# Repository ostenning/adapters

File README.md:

# adapters
A collection of smd to through-hole adapters

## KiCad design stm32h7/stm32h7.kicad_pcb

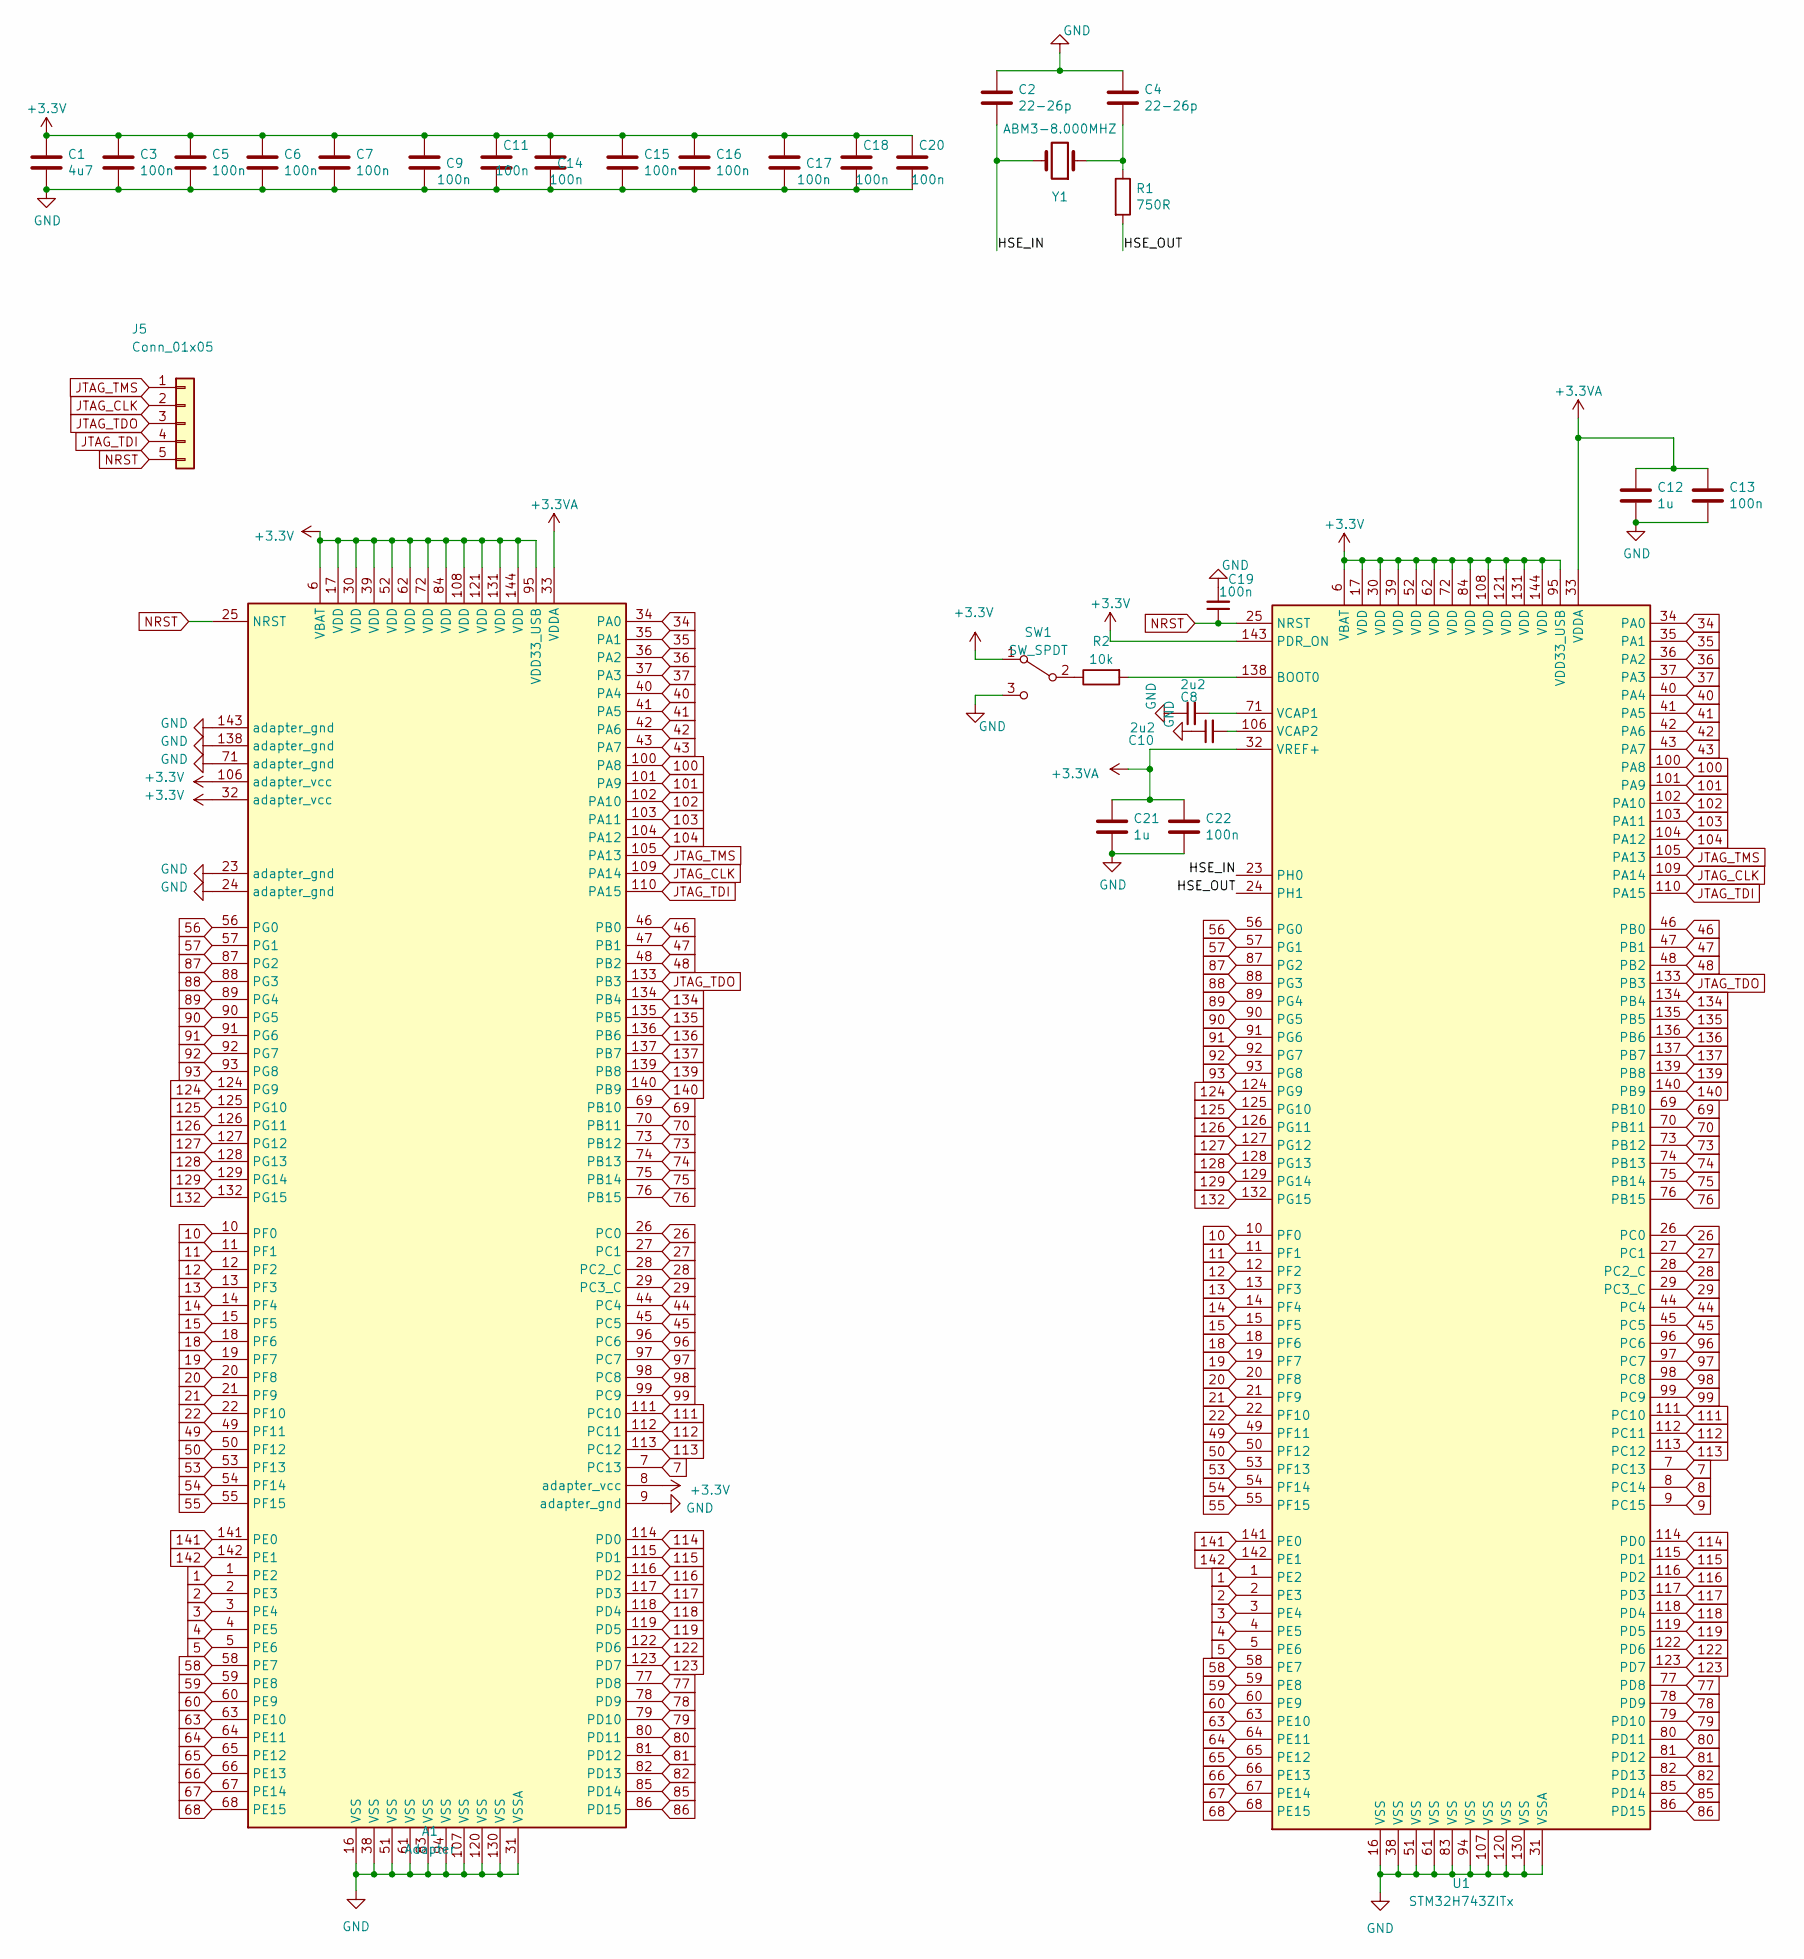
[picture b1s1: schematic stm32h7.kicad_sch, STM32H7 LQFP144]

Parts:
A1: Adapter; stm32h7_adapter
C1: 4u7; C_0603_1608Metric; LCSC Part # C19666
C2, C4: 22-26p; C_0402_1005Metric; LCSC Part # C388039
C3, C5, C6, C7, C9, C11, C13, C14, C15, C16, C17, C18, C20, C22: 100n; C_0603_1608Metric; LCSC Part # C14663
C8, C10: 2u2; C_0603_1608Metric; LCSC C23630
C12, C21: 1u; C_0603_1608Metric; LCSC Part # C15849
C19: 100n; C_0603_1608Metric; LCSC C14663
J5: Conn_01x05; PinHeader_1x05_P2.00mm_Vertical
R1: 750R; R_0603_1608Metric; LCSC Part # C23241
R2: 10k; R_0603_1608Metric; LCSC C25804
SW1: SW_SPDT; PinHeader_1x03_P2.54mm_Vertical
U1: STM32H743ZITx; LQFP-144_20x20mm_P0.5mm
Y1: ABM3-8.000MHZ; Crystal_SMD_Abracon_ABM3-2Pin_5.0x3.2mm_HandSoldering

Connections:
1: A1.1 (PE2), U1.1 (PE2)
2: A1.2 (PE3), U1.2 (PE3)
3: A1.3 (PE4), U1.3 (PE4)
4: A1.4 (PE5), U1.4 (PE5)
5: A1.5 (PE6), U1.5 (PE6)
7: A1.7 (PC13), U1.7 (PC13)
10: A1.10 (PF0), U1.10 (PF0)
11: A1.11 (PF1), U1.11 (PF1)
12: A1.12 (PF2), U1.12 (PF2)
13: A1.13 (PF3), U1.13 (PF3)
14: A1.14 (PF4), U1.14 (PF4)
15: A1.15 (PF5), U1.15 (PF5)
18: A1.18 (PF6), U1.18 (PF6)
19: A1.19 (PF7), U1.19 (PF7)
20: A1.20 (PF8), U1.20 (PF8)
21: A1.21 (PF9), U1.21 (PF9)
22: A1.22 (PF10), U1.22 (PF10)
26: A1.26 (PC0), U1.26 (PC0)
27: A1.27 (PC1), U1.27 (PC1)
28: A1.28 (PC2_C), U1.28 (PC2_C)
29: A1.29 (PC3_C), U1.29 (PC3_C)
34: A1.34 (PA0), U1.34 (PA0)
35: A1.35 (PA1), U1.35 (PA1)
36: A1.36 (PA2), U1.36 (PA2)
37: A1.37 (PA3), U1.37 (PA3)
40: A1.40 (PA4), U1.40 (PA4)
41: A1.41 (PA5), U1.41 (PA5)
42: A1.42 (PA6), U1.42 (PA6)
43: A1.43 (PA7), U1.43 (PA7)
44: A1.44 (PC4), U1.44 (PC4)
45: A1.45 (PC5), U1.45 (PC5)
46: A1.46 (PB0), U1.46 (PB0)
47: A1.47 (PB1), U1.47 (PB1)
48: A1.48 (PB2), U1.48 (PB2)
49: A1.49 (PF11), U1.49 (PF11)
50: A1.50 (PF12), U1.50 (PF12)
53: A1.53 (PF13), U1.53 (PF13)
54: A1.54 (PF14), U1.54 (PF14)
55: A1.55 (PF15), U1.55 (PF15)
56: A1.56 (PG0), U1.56 (PG0)
57: A1.57 (PG1), U1.57 (PG1)
58: A1.58 (PE7), U1.58 (PE7)
59: A1.59 (PE8), U1.59 (PE8)
60: A1.60 (PE9), U1.60 (PE9)
63: A1.63 (PE10), U1.63 (PE10)
64: A1.64 (PE11), U1.64 (PE11)
65: A1.65 (PE12), U1.65 (PE12)
66: A1.66 (PE13), U1.66 (PE13)
67: A1.67 (PE14), U1.67 (PE14)
68: A1.68 (PE15), U1.68 (PE15)
69: A1.69 (PB10), U1.69 (PB10)
70: A1.70 (PB11), U1.70 (PB11)
73: A1.73 (PB12), U1.73 (PB12)
74: A1.74 (PB13), U1.74 (PB13)
75: A1.75 (PB14), U1.75 (PB14)
76: A1.76 (PB15), U1.76 (PB15)
77: A1.77 (PD8), U1.77 (PD8)
78: A1.78 (PD9), U1.78 (PD9)
79: A1.79 (PD10), U1.79 (PD10)
80: A1.80 (PD11), U1.80 (PD11)
81: A1.81 (PD12), U1.81 (PD12)
82: A1.82 (PD13), U1.82 (PD13)
85: A1.85 (PD14), U1.85 (PD14)
86: A1.86 (PD15), U1.86 (PD15)
87: A1.87 (PG2), U1.87 (PG2)
88: A1.88 (PG3), U1.88 (PG3)
89: A1.89 (PG4), U1.89 (PG4)
90: A1.90 (PG5), U1.90 (PG5)
91: A1.91 (PG6), U1.91 (PG6)
92: A1.92 (PG7), U1.92 (PG7)
93: A1.93 (PG8), U1.93 (PG8)
96: A1.96 (PC6), U1.96 (PC6)
97: A1.97 (PC7), U1.97 (PC7)
98: A1.98 (PC8), U1.98 (PC8)
99: A1.99 (PC9), U1.99 (PC9)
100: A1.100 (PA8), U1.100 (PA8)
101: A1.101 (PA9), U1.101 (PA9)
102: A1.102 (PA10), U1.102 (PA10)
103: A1.103 (PA11), U1.103 (PA11)
104: A1.104 (PA12), U1.104 (PA12)
111: A1.111 (PC10), U1.111 (PC10)
112: A1.112 (PC11), U1.112 (PC11)
113: A1.113 (PC12), U1.113 (PC12)
114: A1.114 (PD0), U1.114 (PD0)
115: A1.115 (PD1), U1.115 (PD1)
116: A1.116 (PD2), U1.116 (PD2)
117: A1.117 (PD3), U1.117 (PD3)
118: A1.118 (PD4), U1.118 (PD4)
119: A1.119 (PD5), U1.119 (PD5)
122: A1.122 (PD6), U1.122 (PD6)
123: A1.123 (PD7), U1.123 (PD7)
124: A1.124 (PG9), U1.124 (PG9)
125: A1.125 (PG10), U1.125 (PG10)
126: A1.126 (PG11), U1.126 (PG11)
127: A1.127 (PG12), U1.127 (PG12)
128: A1.128 (PG13), U1.128 (PG13)
129: A1.129 (PG14), U1.129 (PG14)
132: A1.132 (PG15), U1.132 (PG15)
134: A1.134 (PB4), U1.134 (PB4)
135: A1.135 (PB5), U1.135 (PB5)
136: A1.136 (PB6), U1.136 (PB6)
137: A1.137 (PB7), U1.137 (PB7)
139: A1.139 (PB8), U1.139 (PB8)
140: A1.140 (PB9), U1.140 (PB9)
141: A1.141 (PE0), U1.141 (PE0)
142: A1.142 (PE1), U1.142 (PE1)
+3.3VA: A1.33 (VDDA), C12.1, C13.1, C21.1, C22.1, U1.32 (VREF+), U1.33 (VDDA)
+3V3: A1.6 (VBAT), A1.8 (adapter_vcc), A1.17 (VDD), A1.30 (VDD), A1.32 (adapter_vcc), A1.39 (VDD), A1.52 (VDD), A1.62 (VDD), A1.72 (VDD), A1.84 (VDD), A1.95 (VDD33_USB), A1.106 (adapter_vcc), A1.108 (VDD), A1.121 (VDD), A1.131 (VDD), A1.144 (VDD), C1.1, C3.1, C5.1, C6.1, C7.1, C9.1, C11.1, C14.1, C15.1, C16.1, C17.1, C18.1, C20.1, SW1.1 (A), U1.6 (VBAT), U1.17 (VDD), U1.30 (VDD), U1.39 (VDD), U1.52 (VDD), U1.62 (VDD), U1.72 (VDD), U1.84 (VDD), U1.95 (VDD33_USB), U1.108 (VDD), U1.121 (VDD), U1.131 (VDD), U1.143 (PDR_ON), U1.144 (VDD)
/HSE_IN: C2.2, U1.23 (PH0), Y1.2
/HSE_OUT: R1.2, U1.24 (PH1)
GND: A1.9 (adapter_gnd), A1.16 (VSS), A1.23 (adapter_gnd), A1.24 (adapter_gnd), A1.31 (VSSA), A1.38 (VSS), A1.51 (VSS), A1.61 (VSS), A1.71 (adapter_gnd), A1.83 (VSS), A1.94 (VSS), A1.107 (VSS), A1.120 (VSS), A1.130 (VSS), A1.138 (adapter_gnd), A1.143 (adapter_gnd), C1.2, C2.1, C3.2, C4.1, C5.2, C6.2, C7.2, C8.1, C9.2, C10.1, C11.2, C12.2, C13.2, C14.2, C15.2, C16.2, C17.2, C18.2, C19.2, C20.2, C21.2, C22.2, SW1.3 (C), U1.16 (VSS), U1.31 (VSSA), U1.38 (VSS), U1.51 (VSS), U1.61 (VSS), U1.83 (VSS), U1.94 (VSS), U1.107 (VSS), U1.120 (VSS), U1.130 (VSS)
JTAG_CLK: A1.109 (PA14), J5.2, U1.109 (PA14)
JTAG_TDI: A1.110 (PA15), J5.4, U1.110 (PA15)
JTAG_TDO: A1.133 (PB3), J5.3, U1.133 (PB3)
JTAG_TMS: A1.105 (PA13), J5.1, U1.105 (PA13)
NRST: A1.25 (NRST), C19.1, J5.5, U1.25 (NRST)
unnamed: C4.2, R1.1, Y1.1
unnamed: R2.1, SW1.2 (B)
unnamed: R2.2, U1.138 (BOOT0)
unnamed: C8.2, U1.71 (VCAP1)
unnamed: C10.2, U1.106 (VCAP2)

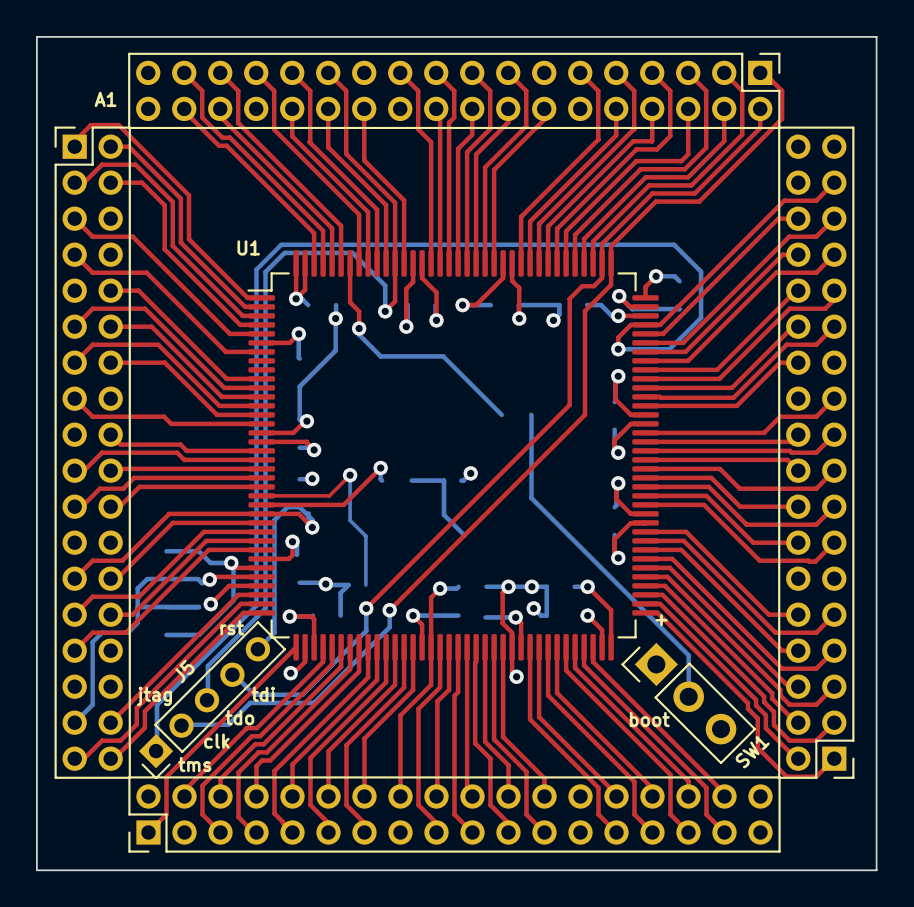
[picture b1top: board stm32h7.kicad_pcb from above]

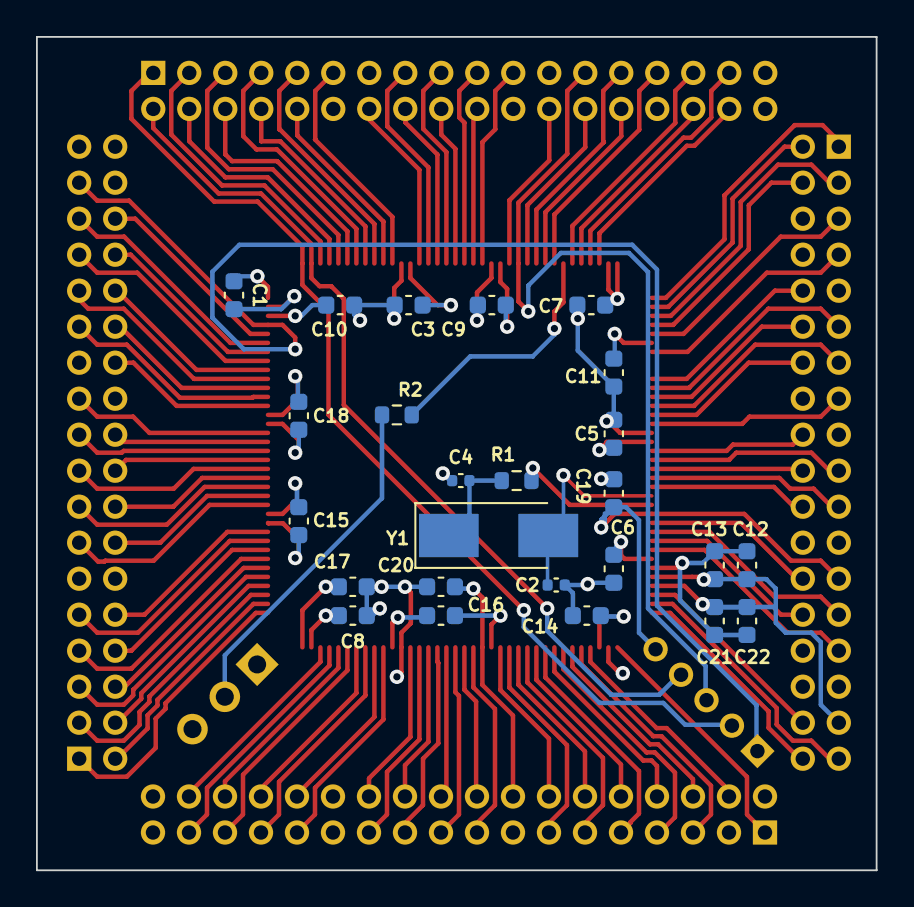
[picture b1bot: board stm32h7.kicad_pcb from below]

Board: 4 copper layers, 46.6 x 46.3 mm, 29 parts (25 on the bottom side), 121 nets.

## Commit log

2021-07-25 add htssop24 adapter
2021-07-26 gerber file for htssop24
2021-07-26 add stm32h7 adapter
2021-07-27 add gerber for stm32h7
2021-07-27 update stm32h7 gerber and assembly
2021-09-06 add dedicated symbol and footprint for easier porting
2021-09-12 update stm32h7 adapter
